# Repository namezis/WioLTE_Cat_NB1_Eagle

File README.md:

# WioLTE_Cat_NB1_Documents

Split [Wio LTE Cat NB1 v1.02.sch](https://github.com/namezis/WioLTE_Cat_NB1_Eagle/blob/master/eagle/Wio%20LTE%20Cat%20NB1%20v1.02%20-%20Schematic%20-%20ANNOTATE.pdf) into seperate pages.

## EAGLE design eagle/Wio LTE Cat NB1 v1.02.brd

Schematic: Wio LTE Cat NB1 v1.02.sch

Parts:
ANT1, ANT2: U-FL; U-FL3P-SMD-2.6X2.6X1.0MM
C1, C3, C22, C25, C29, C31, C50, C52, C56, C58, C60, C62, C64, C66, C75, C77, C78, C83, C84, C85, C87, C90: 100nF; C0402
C2, C10, C51, C68, C69, C70, C71, C72, C89: 10uF; C0603
C4, C80, C88: 22uF; C0805
C5, C20, C21: 0R; C0402
C6, C7, C30: DNP; C0402
C8, C9: 22pF; C0402
C11, C12, C13, C14, C15, C16, C17, C18, C19, C33, C34, C35, C36, C37, C38, C41, C42, C43, C44, C45, C46, C47, C48, C49, C53, C54, C55: 33pF; C0402
C23, C24: DNP; AVX-D
C26, C73: 10nF; C0402
C27: 68pF; C0402
C28: 15pF; C0402
C32: 1uF; C0603
C39, C40: 4.7uF; C0402
C57, C59, C61, C63, C65, C67, C74, C76, C79, C86: 1uF; C0402
C81: 10uF; C0805
C82: 4.7uF; C0603
D1: DNP; SOD-123
D2, D20, D23: RED; LED-0402
D3, D5, D6, D7, D8, D9, D10, D11, D12, D13, D14, D16, D19, D22, D24: DNP; ESD-0402
D4: YELLOW; LED-0402
D15: Blue; LED-0402
D17, D18: ESDPSA0402V05; ESD-0402
D21: GREEN; LED-0402
D25: DNP; SOD-523
F1: SMD1210R200SF; F1210
FR1, FR2, FR3, FR4, FR5, FR6, FR7, FR8: SEEEDSTUDIO-OPEN-SCH-FRAME; SEEEDSTUDIO-PCB-FRAME
J1, J2, J3, J4, J5, J7: GROVE; HW4-SMD-2.0-90D
J6: HC55-SIM20-250; SIM+TF-24P-SMD-1.2-15.05X13.66X2.5MM
J8: DNP; H5-SMD-2.0-TEST
J9: USB-MC-001-05; MICRO-USB5+5P-SMD-0.65-7.2X5.06MM
J10: JST-2P-SMD-90D; HW2-SMD-2.0-90D
K1: SKRPADE010; SW4P-SMD-4.5X3.2X2.5MM
K2, K3: SKRPABE010; SW4P-SMD-4.5X3.2X2.5MM
L1: 27nH; L0402
L3, L4: DNP; L0402
L5: 30R/3000mA; L0603
L6: 1uH; L201610
L7: SPH25201H1R2MT; L2520
LED1: SK6812MINI; LED4-1.75-3.7X3.5X0.95MM
Q1, Q3, Q4, Q10, Q13: NCE3407A; SOT-23
Q2, Q5, Q6, Q7, Q8, Q9, Q11, Q12, Q14: BSS138LT3G; SOT-23
R1, R14, R20, R63, R84: 470k; R0402
R2, R6, R23, R28, R29, R30, R31, R32, R33, R34, R61, R76, R77, R94, R95, R107: DNP; R0402
R3, R4, R8, R10, R11, R12, R13, R15, R16, R17, R18, R19, R22, R35, R36, R38, R39, R40, R41, R44, R45, R47, R53, R55, R56, R59, R67, R68, R70, R78, R79, R86, R87, R90, R93, R97: 0R; R0402
R5, R21, R25, R26, R46, R51, R52, R58, R69, R71, R72, R88, R91, R92, R99: 1k; R0402
R7, R24, R27, R73, R89: 1M; R0402
R37: 15k; R0402
R42, R43, R66, R105: 4.7k; R0402
R48, R49, R57, R64, R65, R80, R81: 22R; R0402
R50, R54, R62, R101, R103, R106: 10k; R0402
R60, R74, R75, R82: 100k; R0402
R83: 150k_1%; R0402
R85: 33k_1%; R0402
R96: 20k; R0402
R98: 24k_1%; R0402
R100: 2.7k_1%; R0402
R102: 10k_1%; R0402
R104, R109: 10M; R0402
R108: 2k; R0402
TP1, TP2, TP3, TP4, TP5, TP7, TP8, TP9, TP10, TP11, TP12, TP13, TP14, TP15, TP16, TP17, TP19: TEST-POINT'4545'; TP-D45MIL
U1: MAX-M8Q; LGA18-1.1-9.7X10.1X2.5MM
U3: STM32F405RGT6; LQFP64
U4: SARA-R410M; MOUDLE96P-SMD-1.1-26X16X2.53MM
U5: MP2161GJ; TSOT23-8
U6: MP2617B; QFN20-0.5-3X4X1MM
U7: TXS0108E; TSSOP20-0.65-6.5X4.4MM
X1: 32.768KHZ; X2-SMD-L2.0X1.2X0.55MM
X2: 8M; RESONATOR3-SMD-3.6X1.3X0.8MM

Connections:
5V: C81.1, C82.1, C83.1, D16.2, F1.2, R22.1, R96.1, TP15.T, U6.3 (IN)
A4: R36.2, U3.20 (PA4)
A5: R39.2, U3.21 (PA5)
A6: R12.2, U3.22 (PA6)
A7: R16.2, U3.23 (PA7)
BAT_C: C90.1, R104.1, R109.2, U3.26 (PB0)
BOOT0: D24.2, K1.4 (B1), R74.1, U3.60 (BOOT0)
BOOT1: R61.1, R62.2, U3.28 (PB2)
CD/DATA3: C46.1, D11.2, J6.T2 (CD/DAT3), R30.2, R45.1
D19: R15.2, U3.55 (PB3)
D20: R11.2, U3.56 (PB4)
D38: R10.2, U3.37 (PC6)
D39: R13.2, U3.38 (PC7)
GND: ANT1.GND1, ANT1.GND2, ANT2.GND1, ANT2.GND2, C1.2, C2.2, C3.2, C4.1, C6.1, C7.1, C8.2, C9.2, C10.2, C11.2, C12.2, C13.2, C14.2, C15.2, C16.2, C17.2, C18.2, C19.2, C22.2, C23.-, C24.-, C25.1, C26.1, C27.1, C28.1, C29.2, C30.2, C31.2, C32.2, C33.2, C34.2, C35.2, C36.2, C37.2, C38.2, C39.1, C40.1, C41.2, C42.2, C43.2, C44.2, C45.2, C46.2, C47.2, C48.2, C49.2, C50.1, C51.2, C52.2, C53.2, C54.2, C55.2, C56.1, C57.1, C58.1, C59.1, C60.1, C61.1, C62.1, C63.1, C64.1, C65.1, C66.1, C67.1, C68.2, C69.1, C70.1, C71.1, C72.1, C73.1, C74.1, C75.2, C76.1, C78.1, C79.1, C80.1, C81.2, C82.2, C83.2, C84.1, C85.1, C86.1, C87.1, C88.2, C89.2, C90.2, D1.+, D3.1, D5.1, D6.1, D7.1, D8.1, D9.1, D10.1, D11.1, D12.1, D13.1, D14.1, D16.1, D17.1, D18.1, D19.1, D22.1, D24.1, D25.+, J1.4, J1.SS1, J1.SS2, J2.4, J2.SS1, J2.SS2, J3.4, J3.SS1, J3.SS2, J4.4, J4.SS1, J4.SS2, J5.4, J5.SS1, J5.SS2, J6.P5 (GND), J6.P5B (GND), J6.PAD, J6.PAD1 (PAD), J6.PAD2 (PAD), J6.PAD3 (PAD), J6.T6 (VSS), J7.4, J7.SS1, J7.SS2, J8.2, J9.5 (GND), J9.P1 (GND), J9.P3 (GND), J9.P4 (GND), J9.P5 (GND), J9.P6 (GND), J10.3, J10.4, J10.- (2), L3.1, LED1.2 (VSS), Q2.2 (S), Q5.2 (S), Q6.2 (S), Q7.2 (S), Q8.2 (S), Q9.2 (S), Q11.2 (S), Q12.2 (S), Q14.2 (S), R7.1, R24.1, R27.1, R50.2, R54.2, R55.1, R60.2, R62.1, R73.1, R74.2, R75.2, R86.2, R87.1, R89.1, R93.2, R94.2, R95.2, R101.2, R102.1, R106.2, R107.1, R108.1, R109.1, TP14.T, TP19.T, U1.1 (GND), U1.10 (GND), U1.12 (GND), U3.12 (VSSA/VREF-), U3.18 (VSS), U3.63 (VSS), U4.1 (GND), U4.3 (GND), U4.5 (GND), U4.14 (GND), U4.20 (GND), U4.21 (GND), U4.22 (GND), U4.30 (GND), U4.32 (GND), U4.43 (GND), U4.50 (GND), U4.54 (GND), U4.55 (GND), U4.57 (GND), U4.58 (GND), U4.59 (GND), U4.60 (GND), U4.61 (GND), U4.63 (GND), U4.64 (GND), U4.65 (GND), U4.66 (GND), U4.67 (GND), U4.68 (GND), U4.69 (GND), U4.70 (GND), U4.71 (GND), U4.72 (GND), U4.73 (GND), U4.74 (GND), U4.75 (GND), U4.76 (GND), U4.77 (GND), U4.78 (GND), U4.79 (GND), U4.80 (GND), U4.81 (GND), U4.82 (GND), U4.83 (GND), U4.84 (GND), U4.85 (GND), U4.86 (GND), U4.87 (GND), U4.88 (GND), U4.89 (GND), U4.90 (GND), U4.91 (GND), U4.92 (GND), U4.93 (GND), U4.94 (GND), U4.95 (GND), U4.96 (GND), U5.4 (PGND), U5.6 (AGND), U6.5 (PGND), U6.6 (!EN), U6.11 (AGND), U7.11 (GND), X2.2
GNSS_1PPS: R6.2, U3.36 (PB15)
GNSS_INT: R4.2, U3.10 (PC2)
GNSS_PWER: R5.2, U3.33 (PB12)
GNSS_RST: R2.2, U3.9 (PC1)
GPIO3: TP7.T, U4.24 (GPIO3)
GPIO4: TP8.T, U4.25 (GPIO4)
GRO_POWR: R71.2, U3.8 (PC0)
I2C1_SCL: R43.1, R67.2, U3.61 (PB8)
I2C1_SDA: R42.1, R68.2, U3.62 (PB9)
JTCK-SWCLK: R78.1, U3.49 (PA14)
JTMS-SWDIO: R79.1, U3.46 (PA13)
LED_RGB: LED1.3 (DIN), U3.27 (PB1)
LNA_EN: U1.13 (LNA_EN)
LTE_1V8: C84.2, R105.2, U4.4 (V_INT), U7.2 (VCCA)
LTE_POWER: R23.1, R25.2, U3.57 (PB5)
MPS_VCC: C86.2, R99.1, R103.1, U6.20 (VCC)
unnamed: C73.2, L1.1, R8.2
unnamed: TP13.T, U5.1 (PG)
unnamed: K3.4 (B1), R93.1
unnamed: R64.1, U4.28 (USB_D-)
unnamed: R65.1, U4.29 (USB_D+)
unnamed: D20.-, R91.2
unnamed: C76.2, LED1.4 (VDD), R90.2
unnamed: C75.1, Q14.1 (G), R88.1, R89.2
unnamed: R103.2, R106.1, U6.16 (NTC)
unnamed: C20.2, U4.56 (ANT)
unnamed: D2.+, R26.2
unnamed: K2.4 (B1), R86.1
unnamed: Q13.1 (G), Q14.3 (D), R84.1
unnamed: Q7.1 (G), R46.1, R50.1
unnamed: C39.2, U3.31 (VCAP_1)
unnamed: C40.2, U3.47 (VCAP_2)
unnamed: J8.3, R76.1, R78.2
unnamed: J8.4, R77.1, R79.2
unnamed: R98.1, R100.2
unnamed: R100.1, R102.2, U6.12 (SYSFB)
unnamed: F1.1, J9.1 (VCC), TP9.T
unnamed: Q4.1 (G), Q6.3 (D), R20.1
unnamed: C29.1, Q6.1 (G), R25.1, R27.2
unnamed: Q8.1 (G), R51.1, R54.1
unnamed: Q8.3 (D), TP2.T, U4.18 (RESET_N)
unnamed: Q12.1 (G), R72.2, R75.1
unnamed: C87.2, U6.18 (TMR)
unnamed: K1.2 (A1), R66.1
unnamed: C77.2, L7.1, U6.2 (SW), U6.4 (SW)
unnamed: C45.1, D10.2, J6.T1 (DAT2), R29.2, R44.1
unnamed: C44.1, D9.2, J6.T8 (DAT1), R28.2, R59.1
unnamed: R107.2, U6.17 (ILIM)
unnamed: R108.2, U6.15 (ISET)
unnamed: R72.1, U4.16 (GPIO1)
unnamed: R58.1, U4.23 (GPIO2)
unnamed: C77.1, U6.1 (BST)
unnamed: C53.1, J7.3, R70.1
unnamed: R96.2, R97.1
unnamed: C54.1, J7.2, R68.1
unnamed: Q9.1 (G), R58.2, R60.1
unnamed: C55.1, J7.1, R67.1
unnamed: R55.2, U4.9 (DTR)
unnamed: C16.1, J1.3, R17.1
unnamed: R85.2, R87.2
unnamed: L6.1, U5.3 (SW)
unnamed: Q9.3 (D), R52.1
unnamed: C15.1, J1.2, R13.1
unnamed: D18.2, J9.3 (DP), R81.1, TP12.T
unnamed: C14.1, J1.1, R10.1
unnamed: D17.2, J9.2 (DM), R80.1, TP11.T
unnamed: D21.-, R92.2
unnamed: Q12.3 (D), R69.1
unnamed: C20.1, C21.2, L3.2
unnamed: C43.1, D7.2, J6.P2 (RST), J6.P2B (RST), R48.2
unnamed: C42.1, D6.2, J6.P3 (CLK1), J6.P3B (CLK1), R49.2
unnamed: R34.1, U4.62 (ANT_DET)
unnamed: C41.1, D5.2, J6.P7 (I/O), J6.P7B (I/O), R37.2, R57.2
unnamed: C17.1, J2.3, R18.1
unnamed: C18.1, J2.2, R15.1
unnamed: C19.1, J2.1, R11.1
unnamed: C30.1, D3.2, L4.2, R34.2
unnamed: C11.1, J3.3, R19.1
unnamed: Q3.1 (G), Q5.3 (D), R14.1
unnamed: C12.1, J3.2, R16.1
unnamed: C13.1, J3.1, R12.1
unnamed: C33.1, J4.3, R40.1
unnamed: R82.2, U5.8 (EN)
unnamed: C34.1, J4.2, R38.1
unnamed: C35.1, J4.1, R35.1
unnamed: C36.1, J5.3, R41.1
unnamed: C37.1, J5.2, R39.1
unnamed: C38.1, J5.1, R36.1
unnamed: R83.1, R85.1, U5.7 (FB)
unnamed: Q10.1 (G), Q11.3 (D), R63.1
unnamed: C52.1, Q11.1 (G), R71.1, R73.2
unnamed: R97.2, R101.1, U6.19 (VLIM)
unnamed: R94.1, U6.7 (M0)
unnamed: R95.1, U6.8 (M1)
unnamed: C22.1, Q5.1 (G), R21.1, R24.2
unnamed: Q1.1 (G), Q2.3 (D), R1.1
unnamed: D23.-, U6.9 (!CHGOK)
unnamed: D23.+, R99.2
unnamed: ANT1.D, C5.1, C7.2, L1.2
unnamed: ANT2.D, C21.1, L4.1
unnamed: D4.-, R52.2
unnamed: R2.1, U1.9 (RESET_N)
unnamed: R3.1, U1.6 (V_BCKP)
unnamed: R4.1, U1.5 (EXTINT)
unnamed: R6.1, U1.4 (TIMEPULSE)
unnamed: D15.-, R69.2
unnamed: C3.1, Q2.1 (G), R5.1, R7.2
NRST: C31.1, D2.-, D19.2, J8.5, K2.2 (A1), U3.7 (NRST)
OE: R105.1, U7.10 (OE)
OSC32_IN: C8.1, U3.3 (PC14-OSC32_IN), X1.1
OSC32_OUT: C9.1, U3.4 (PC15-OSC32_OUT), X1.2
OSC_IN: U3.5 (PH0-OSC_IN), X2.1
OSC_OUT: U3.6 (PH1-OSC_OUT), X2.3
PWRKEY: D22.2, K3.2 (A1), Q7.3 (D), TP1.T, U4.15 (PWR_ON)
PWRKEY_MODULE: R46.2, U3.24 (PC4)
RESET_MODULE: R51.2, U3.11 (PC3)
RF_IN: C5.2, C6.2, U1.11 (RF_IN)
RGB_POWR: R88.2, U3.41 (PA8)
RX_LED: R92.1, U3.34 (PB13)
SARA_CTS: U4.11 (CTS), U7.5 (A4)
SARA_RTS: U4.10 (RTS), U7.4 (A3)
SARA_RX: U4.13 (RXD), U7.1 (A1)
SARA_TX: U4.12 (TXD), U7.3 (A2)
SDIO_CK: R53.2, U3.53 (PC12)
SDIO_CMD: R47.2, U3.54 (PD2)
SDIO_D0: R56.2, U3.39 (PC8)
SDIO_D1: R59.2, U3.40 (PC9)
SDIO_D2: R44.2, U3.51 (PC10)
SDIO_D3: R45.2, U3.52 (PC11)
SD_CLK: C48.1, D13.2, J6.T5 (CLK), R32.2, R53.1
SD_CMD: C47.1, D12.2, J6.T3 (CMD), R31.2, R47.1
SD_DATA0: C49.1, D14.2, J6.T7 (DAT0), R33.2, R56.1
SD_POWR: R21.2, U3.50 (PA15)
TX_LED: R91.1, U3.35 (PB14)
USART1_RX: R35.2, U3.59 (PB7)
USART1_TX: R38.2, U3.58 (PB6)
USART2_CTS: U3.14 (PA0), U7.16 (B4)
USART2_RTS: U3.15 (PA1), U7.17 (B3)
USART2_RX: U3.17 (PA3), U7.20 (B1)
USART2_TX: U3.16 (PA2), U7.18 (B2)
USART3_RX: U1.2 (TXD), U3.30 (PB11)
USART3_TX: U1.3 (RXD), U3.29 (PB10)
USB_DM: R64.2, TP4.T
USB_DP: R65.2, TP5.T
USB_FS_DM: R80.2, U3.44 (PA11)
USB_FS_DP: R81.2, U3.45 (PA12)
USB_FS_VBUS: R22.2, U3.42 (PA9)
USB_VBUS: TP3.T, U4.17 (VUSB_DET)
USIM_CLK: R49.1, U4.38 (SIM_CLK)
USIM_DATA: R57.1, U4.39 (SIM_IO)
USIM_RST: R48.1, U4.40 (SIM_RST)
USIM_VDD: D8.2, J6.P1 (VCC), J6.P1B (VCC), R37.1, U4.41 (VSIM)
VBAT: C88.1, C89.1, D25.-, J10.+ (1), R104.2, TP17.T, U6.14 (BATT)
VCC_RF: R8.1, U1.14 (VCC_RF)
VDDA/VREF+: C32.1, C66.2, C67.2, L5.2, U3.13 (VDDA/VREF+)
VDD_3V3: C56.2, C57.2, C58.2, C59.2, C60.2, C61.2, C62.2, C63.2, C64.2, C65.2, C71.2, C72.2, C85.2, D4.+, D15.+, D20.+, D21.+, J8.1, L5.1, L6.2, Q1.2 (S), Q3.2 (S), Q10.2 (S), Q13.2 (S), R1.2, R14.2, R17.2, R23.2, R26.1, R42.2, R43.2, R61.2, R63.2, R66.2, R76.2, R77.2, R83.2, R84.2, TP10.T, U3.1 (VBAT), U3.19 (VDD), U3.32 (VDD), U3.48 (VDD), U3.64 (VDD), U5.5 (OUT), U7.19 (VCCB)
VDD_3V3_B: C51.1, Q10.3 (D), R18.2, R19.2, R40.2, R41.2, R70.2
VDD_3V3_RGB: C68.1, Q13.3 (D), R90.1
VDD_3V3_SD: C10.1, C50.2, J6.T4 (VDD), Q3.3 (D), R28.1, R29.1, R30.1, R31.1, R32.1, R33.1
VDD_GNSS: C1.1, C2.1, Q1.3 (D), R3.2, U1.7 (VCC_IO), U1.8 (VCC)
VLTE: C23.+, C24.+, C25.2, C26.2, C27.2, C28.2, D1.-, Q4.3 (D), U4.51 (VCC), U4.52 (VCC), U4.53 (VCC)
VSYS: C4.2, C69.2, C70.2, C74.2, C78.2, C79.2, C80.2, L7.2, Q4.2 (S), R20.2, R82.1, R98.2, TP16.T, U5.2 (VIN), U6.13 (SYS)

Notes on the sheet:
SARA_R410_MODULE
close to VDD
close to VBAT
close to VDDA/VREF+
Initial release
v1.0
2017/7/24
Myer
close to BAT
5V/2A
if charging, LED on. if charging ok, LED off. if blinking, BAT ERROR
close to pin3
≥4.5V
Charge Current:690mA
!ACOK
!CHGOK
Charger Status
low
high
blinking 6Hz
In charging, supplement mode
End of charge, disable charger
NTC fault, timer out
VIN absent, !EN! disable, thermal shutdown
Mode
Low
High
High/Float
USB 2.0(450mA)
USB 3.0(825mA)
Programmable
Default(2A)
USB input current limit
4.26V
70mA
Impedance of RF trace should be controlled by 50 ohm and the length should be kept as short as possible.
D38
D20
UART
I2C

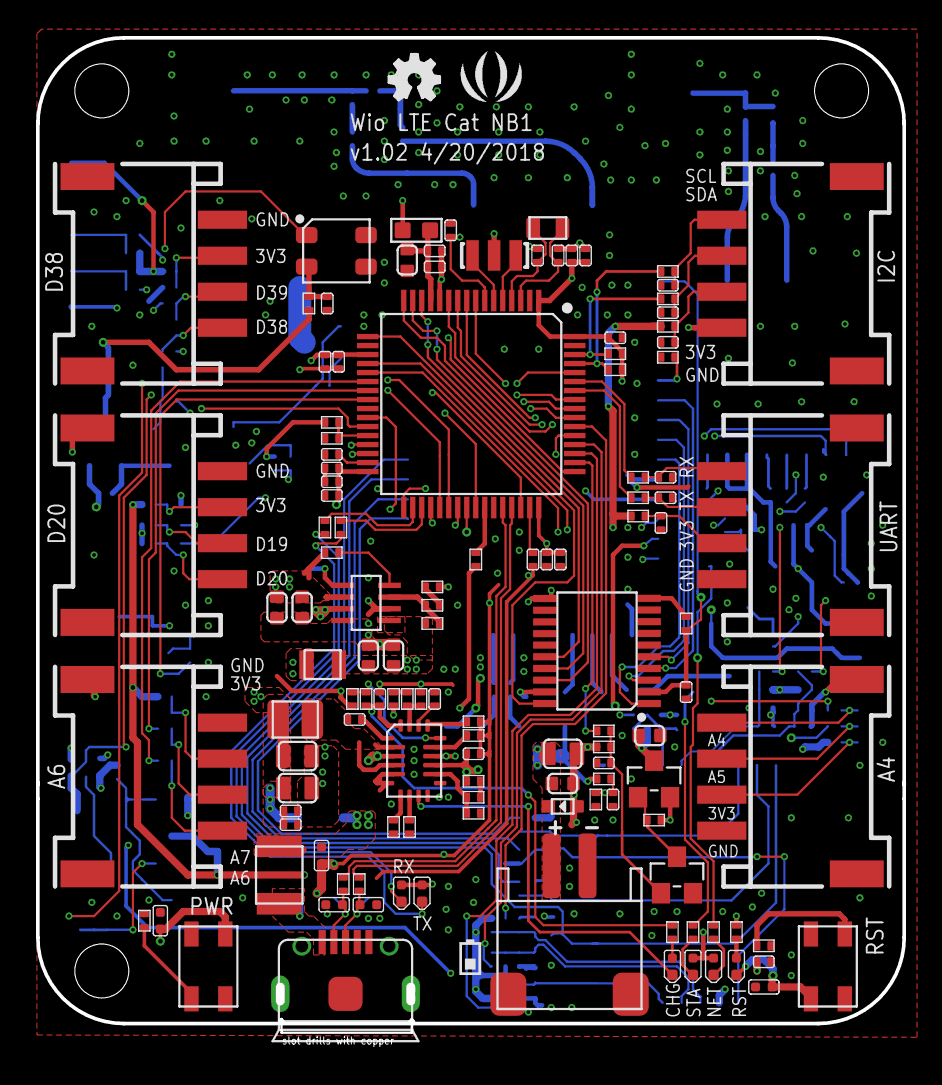
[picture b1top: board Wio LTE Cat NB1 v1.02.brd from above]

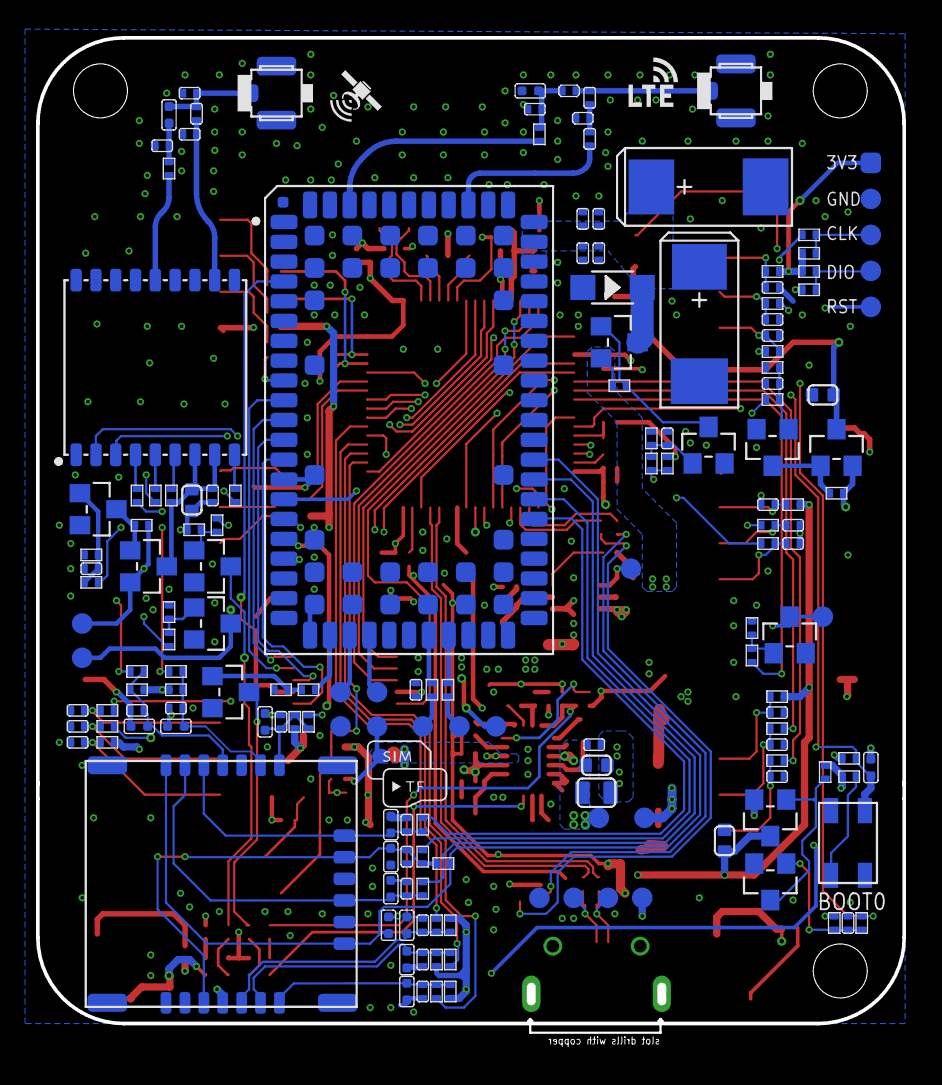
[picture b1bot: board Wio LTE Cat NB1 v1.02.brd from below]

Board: 4 copper layers, 48.1 x 55.3 mm, 295 parts (161 on the bottom side), 175 nets.

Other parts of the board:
U$97: OSHW_FILLX100_NOTEXT
U$98: SEEED-SILK--TNAME-160*153MIL

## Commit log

2018-09-16 Split pages to manageable document reference.
2018-09-16 Add schematics with annotations. Cross check all nets.

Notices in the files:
parts and their libraries:
moudle-new: This work is licensed under the Creative Commons Attribution 4.0 International License.
To view a copy of this license,visit:
http://creativecommons.org/licenses/by-sa/4.0
moudle-new: CC-BY-SA
